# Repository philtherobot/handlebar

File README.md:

### Ergogen

Online design tool at https://ergogen.cache.works/.

Elite-C https://deskthority.net/wiki/Elite-C footprint from ceoloide: https://github.com/ceoloide/ergogen-footprints

Running ergogen:

```
cd handlebar
ergogen . -o output
```

Pass a folder instead of an input file name because handlebar has custom footprints and that's how this works.

### Parts

- Choc v1 switches (Keebd)
- DMK keycaps, 1U (Keebd)
- Elite-C v4, 2 parts (Omega Keys)
- TRRS PJ-320A jack, 2 parts (Clickety Split)
- TRRS cable (Clickety Split)
- Diodes 1N4148W, SOD-123, 50 parts (Digikey 4530-1N4148WCT-ND)
- Push buttons FSMCTTR, 2 parts (Digikey 450-2133-1-ND)
- RGB LEDs FZ2812-5050, QMK compatible (WS2812B) (Digikey, 4544-FZ2812-5050CT-ND)
- MCU socket 801-43-064-10-002000 (Digikey, ED10864-64-ND)
- PCBs, 2 parts
- USB-C/USB cable

The Atmega32u4 on the Elite-C has 32KB flash, 2.5KB SRAM, 16MHz CPU.

#### Base

Mild steel plate, 1/16", 5/64" or 3/32" thick. 1.5mm to 2.5mm thick. 200x150mm or 8"x6", two times.

We plan to either solder the standoff or screw them.

- 8mm long, M2 standoff, 6 times
- dome head M2 screws, 6mm of thread, 6 times
- dome head M2 screws, 4mm of thread, 8 times
- flat head M2 screws, 6mm full length, 6 times
- flat head M2 screws, 10mm full length, 8 times
- M2 nuts, 8 times

### Cost

Elite-C at Omega Keys, 24$ each.
Keycaps and switches, 114$
PCB, JLCPcb, 
TRRS cable
Digi-key

#### Not used, extra
Switches, 13$
TRRS cable, Keebd, 7$ (not used)

### KiCAD 

Tutorial: https://flatfootfox.com/ergogen-part5-kicad-firmware-assembly/

We are better to use constraints from makers. JLCPCB seems to have less capability than others. I found a Kicad board with JLC's capability set. See `JLCPCB_1-2Layer template`.

*DO NOT* edit the elite-c footprint as this will introduce a lot of errors! The errors are introduced because the nets that were setup by Ergogen are lost during the footprint edition.

Steps after ergogen has been executed:
- Import board settings from JLCPCB_1-2Layer template:
  - File/Board Setup/Import from another board. 
  - Turn User.Drawings back on.
  - Change track width to 0.25mm in Net Classes
- add the resistors footprints, R_Axial_DIN0207_L6.3mm_D2.5mm_P10.16mm_Horizontal
  - under the TRRS
  - do not show the reference
- change footprint of indicators to Personal:WS2812B
- (useful: Route/Interactive Router Setting, try Highlight + Free angle or Walk around)
- complete the net connections for the resistors on front of board (VCC on the right, SDA at the top, SCL at the bottom)
- add a via below the indicators for VCC
- wire keys pin 1 (2 of them) to diode 2 on the back
- wire diode pads to holes on the front and back
- wire columns on the back
- route columns around the top and through the middle of the MCU, starting with n_inner
- wire rows on the front: they enter the MCU from the left
- wire reset, place it on the right
- wire VCC on the left of reset *and* go from the second resistor to the via on the *back*
- wire ground, going between n_vcc and n_scl on the TRRS connector, up on the left of VCC
- wire ground to all ground pins on the MCU
- wire SDA from TRRS to the MCU on the back
- indicator grounds
- indicator "next" and to the MCU

Optional:
- give a little bit of space around pads and traces
- add the name and version on the silkscreens

### Fabrication

Prepare Gerber files:
- File/Fabrication/Gerbers
- Check the layers
  - *.Cu, *.Paste, *.Mask, *.Silkscreen, Edge.Cuts
- Set a clean, new, empty directory
- Plot
- Generate drill files
- Zip the output files, flat, no directory

Upload to JLCPCB (https://jlcpcb.com/)

PCB material is FR-4. Use the defaults (1.6mm). Remove JLC's serial numper. Pick your color. 

### Notes

Elite-C information:
- https://deskthority.net/wiki/Elite-C
- Development history, reveals a lot about how it works: https://blog.keeb.io/case-of-the-wayward-elite-c/
- Atmega34U4, Atme AVR

https://flatfootfox.com/ergogen-part3-pcbs/

This has example of adding a PCB via: https://github.com/ergogen/ergogen/blob/675d2709dc4c2515ec34ecf4e5148127495283f3/config.yaml

PCM12 is a sliding switch. (no need it seems)

b3u1000p is a small reset push button. https://www.allaboutcircuits.com/electronic-components/datasheet/B3U-1000P-B--Omron/

This looks close to what I am trying to do: https://github.com/davidphilipbarr/Sweep/tree/main/Sweep%20half-swept

Redox schematic https://github.com/mattdibi/redox-keyboard/blob/master/redox/pcb/Redox-schematic.pdf

# Hardware Checklist

- [x] MCU position on the PCB matches the one in the preview.
- [x] Through holes are the correct size for my components.
- [x] Fit between the diode and the switch.
- [x] Pull up 4.7KΩ resistors, SDA to VCC, SCL to VCC
- [x] Must I²C be connected to those two specific pins? D0 and D1? Yes, let's do that.
- [x] Should I ground all unused pins? No. And there is no need to cover the unused space with ground copper.
- [x] Are the back diodes pads connected to the traces on front? No and I added them.
- [x] Decide on PCB thickness: 1.6mm
- [x] What is the voltage needed by the RGB LEDs? 3V, so VCC is good. Crossed fingers.

# Key Layout

Diagrams are made with [Keyboard Layout Editor](https://www.keyboard-layout-editor.com/).

I have linked the Keyboard Layout Editor account with my Github account. In any case, I saved the diagrams to `key_layout`.

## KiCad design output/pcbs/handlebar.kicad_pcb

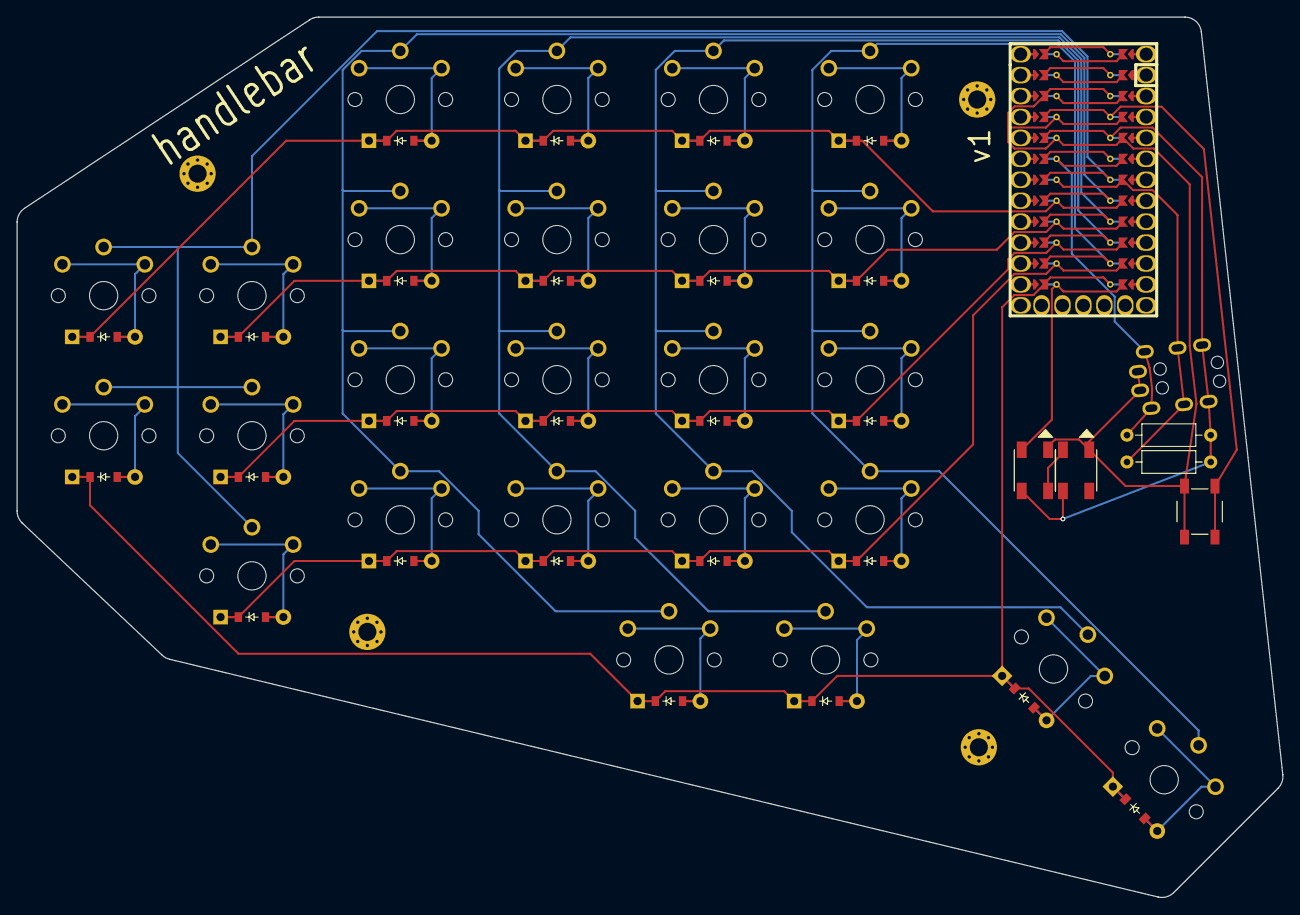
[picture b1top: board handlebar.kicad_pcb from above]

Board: 4 copper layers, 153.6 x 106.8 mm, 58 parts (0 on the bottom side), 38 nets.

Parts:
D1, D2, D3, D4, D5, D6, D7, D8, D9, D10, D11, D12, D13, D14, D15, D16, D17, D18, D19, D20, D21, D22, D23, D24, D25: ComboDiode
I1, I2: WS2812B
S1, S2, S3, S4, S5, S6, S7, S8, S9, S10, S11, S12, S13, S14, S15, S16, S17, S18, S19, S20, S21, S22, S23, S24, S25: PG1350
TRRS1: TRRS-PJ-320A-dual
_2, _3, _4, _5: MountingHole_2.2mm_M2_Pad_Via
rst1: SW_TACT_ALPS_SKQGABE010

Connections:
center_thumb: D24.2, S24.1
index_bottom: D9.2, S9.1
index_home: D10.2, S10.1
index_nums: D12.2, S12.1
index_top: D11.2, S11.1
inner_bottom: D13.2, S13.1
inner_home: D14.2, S14.1
inner_nums: D16.2, S16.1
inner_thumb: D25.2, S25.1
inner_top: D15.2, S15.1
left_thumb: D22.2, S22.1
middle_bottom: D5.2, S5.1
middle_home: D6.2, S6.1
middle_nums: D8.2, S8.1
middle_top: D7.2, S7.1
n_bottom: D1.1, D5.1, D9.1, D13.1, D19.1
n_gnd: I1.33, I2.33, TRRS1.1, rst1.2
n_home: D2.1, D6.1, D10.1, D14.1, D20.1
n_index: S9.2, S10.2, S11.2, S12.2, S24.2
n_indic_next: I1.22, I2.44
n_inner: S13.2, S14.2, S15.2, S16.2, S25.2
n_middle: S5.2, S6.2, S7.2, S8.2, S23.2
n_nums: D4.1, D8.1, D12.1, D16.1, D18.1
n_pinky: S17.2, S18.2, S19.2, S20.2, S21.2
n_ring: S1.2, S2.2, S3.2, S4.2, S22.2
n_thumb: D17.1, D22.1, D23.1, D24.1, D25.1
n_top: D3.1, D7.1, D11.1, D15.1, D21.1
n_vcc: I1.11, I2.11, TRRS1.4
outer_home: D17.2, S17.1
outer_top: D18.2, S18.1
pinky_bottom: D19.2, S19.1
pinky_home: D20.2, S20.1
pinky_top: D21.2, S21.1
right_thumb: D23.2, S23.1
ring_bottom: D1.2, S1.1
ring_home: D2.2, S2.1
ring_nums: D4.2, S4.1
ring_top: D3.2, S3.1

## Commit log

2024-03-25 limited progress on networks
2024-03-25 update kicad files
2024-04-24 Added doc, remove non-source folders, added gitignore
2024-04-24 Added Kicad project
2024-04-25 Nets have started working, diodes
2024-05-02 Board description is now decidely moving towards production. Changed Elite-C footprint for a better one. Clone the diode footprint and removed the through holes. Cloned the Choc footprint in preparat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
2024-05-02 Through hole 2 only added once for the Choc footprint
2024-05-02 Added the reset button, TRRS and two indicator RGB LEDs.
2024-05-03 Adjust TRRS position
2024-05-03 Add mounting holes
2024-05-07 Board description is now decidely moving towards production. Changed Elite-C footprint for a better one. Clone the diode footprint and removed the through holes. Cloned the Choc footprint in preparat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
2024-05-08 Added vias to the diodes. Changed holes for the MCU. Made space for the resistors. Inverted the switches pins to diodes. Rotated the indicators.
2024-05-09 Removed/replaced the "outer" column. Reoriented the indicators. Rearranged the pin assignments. More instructions post-Ergogen.
2024-05-10 Went back to using regular diodes. Kicad JLC template. Updated instructions. Rotated RST.
2024-05-10 Updated gitignore and removed non-source file. This is now the first "I feel like I can produce this" board.
2024-05-10 Updated gitignore
2024-05-10 Changed the big name. Better parts list.
2024-05-20 v1 complete and sent to maker
2024-05-20 Commit the Gerber zip file and the correct footprint library
2026-01-03 Added diagrams of layers
